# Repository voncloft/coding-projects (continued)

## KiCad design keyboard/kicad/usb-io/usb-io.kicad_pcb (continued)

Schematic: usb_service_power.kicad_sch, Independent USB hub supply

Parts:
C50: 10uF 50V X7R; C_1206_3216Metric; MPN CL31B106KBHNNNE; JLCPCB C89632
C51: 100nF 50V X7R; C_0603_1608Metric; MPN CC0603KRX7R9BB104; JLCPCB C14663
C52, C53: 22uF 25V X7R; C_1210_3225Metric; MPN GRM32ER71E226KE15K; JLCPCB C5646288
D10, D11, D12: SS14; D_SMA; MPN SS14; JLCPCB C2480
L1: 4.7uH 4.6A Irms 6A Isat; L_Bourns_SRP5030T; MPN SRP5030T-4R7M
U2: AP63203WU-7; TSOT-23-6; MPN AP63203WU-7; JLCPCB C780769

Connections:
+3V3_HUB: C52.1, C53.1, L1.2, U2.1 (FB); also elsewhere on the board
+5V_CORE: D10.2 (A); also elsewhere on the board
GND: C50.2, C52.2, C53.2, U2.4 (GND); also elsewhere on the board
HUB_BST: C51.1, U2.6 (BST)
HUB_SW: C51.2, L1.1, U2.5 (SW)
PC_VBUS: D11.2 (A); also elsewhere on the board
PD_RAW: D12.2 (A); also elsewhere on the board
SERVICE_IN: C50.1, D10.1 (K), D11.1 (K), D12.1 (K), U2.2 (EN), U2.3 (IN)

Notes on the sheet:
AP63203 fixed 3.3 V. Sources are isolated by 40 V Schottky diodes. The hub stays powered from the connected host/charger during RP2040 reset. Do not connect sources directly.

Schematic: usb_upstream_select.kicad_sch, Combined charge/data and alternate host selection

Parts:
C54, C55: 100nF 50V X7R; C_0603_1608Metric; MPN CC0603KRX7R9BB104; JLCPCB C14663
R54: 10k 1%; R_0603_1608Metric; MPN 0603WAF1002T5E; JLCPCB C25804
R55: 15k 1%; R_0603_1608Metric; MPN 0603WAF1502T5E
U40: TS3USB221ARSER; Texas_UQFN-10_1.5x2mm_P0.5mm; MPN TS3USB221ARSER; JLCPCB C128396
U42: USBLC6-2SC6; SOT-23-6; MPN USBLC6-2SC6; JLCPCB C7519

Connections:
+3V3_HUB: C54.1, C55.1, U40.10 (VCC), U42.5 (VBUS); also elsewhere on the board
CHARGE_DM: U40.2 (1D-), U42.1 (I/O1), U42.6 (I/O1); also elsewhere on the board
CHARGE_DP: U40.1 (1D+), U42.3 (I/O2), U42.4 (I/O2); also elsewhere on the board
GND: C54.2, C55.2, R55.2, U40.5 (GND), U40.6 (OE_N), U42.2 (GND); also elsewhere on the board
PC_DM: U40.4 (2D-); also elsewhere on the board
PC_DP: U40.3 (2D+); also elsewhere on the board
PC_SELECT: R54.2, R55.1, U40.9 (S)
PC_VBUS: R54.1; also elsewhere on the board
UP_DM: U40.7 (D-); also elsewhere on the board
UP_DP: U40.8 (D+); also elsewhere on the board

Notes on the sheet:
Port 1: charging USB-C data. Port 2: existing PC DATA connector. PC takes priority when both are plugged in. Only data is selected; VBUS rails stay isolated. HUSB238 DP/DM are deliberately not connected; USB PD remains on CC1/CC2.

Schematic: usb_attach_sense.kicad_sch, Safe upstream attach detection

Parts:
C56: 100nF 50V X7R; C_0603_1608Metric; MPN CC0603KRX7R9BB104; JLCPCB C14663
Q10, Q11: MMBT3904; SOT-23; MPN MMBT3904; JLCPCB C20526
R50: 220k 1%; R_0603_1608Metric; MPN 0603WAF2203T5E
R51, R52, R53: 100k 1%; R_0603_1608Metric; MPN 0603WAF1003T5E; JLCPCB C25803
R56: 10k 1%; R_0603_1608Metric; MPN 0603WAF1002T5E; JLCPCB C25804
U41: SN74LVC1G04DBVR; SOT-23-5; MPN SN74LVC1G04DBVR

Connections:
+3V3_HUB: C56.1, R56.1, U41.5 (VCC); also elsewhere on the board
GND: C56.2, Q10.2 (E), Q11.2 (E), R51.2, R53.2, U41.3 (GND); also elsewhere on the board
PC_SENSE_BASE: Q11.1 (B), R52.2, R53.1
PC_VBUS: R52.1; also elsewhere on the board
PD_RAW: R50.1; also elsewhere on the board
PD_SENSE_BASE: Q10.1 (B), R50.2, R51.1
UPSTREAM_ABSENT: Q10.3 (C), Q11.3 (C), R56.2, U41.2
UPSTREAM_PRESENT: U41.4; also elsewhere on the board

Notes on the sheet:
Two NPN collectors implement OR presence detection without coupling source VBUS rails. 3.3 V logic drives hub VBUS_DET; the PD input can be 20 V and must never connect directly to this pin.

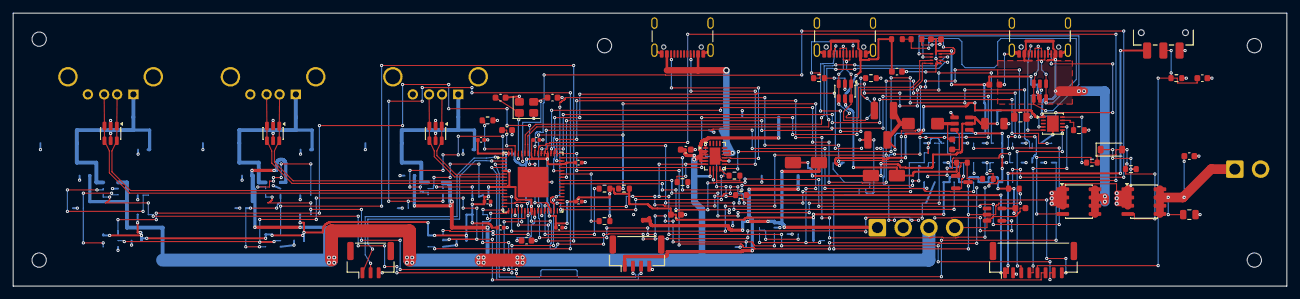
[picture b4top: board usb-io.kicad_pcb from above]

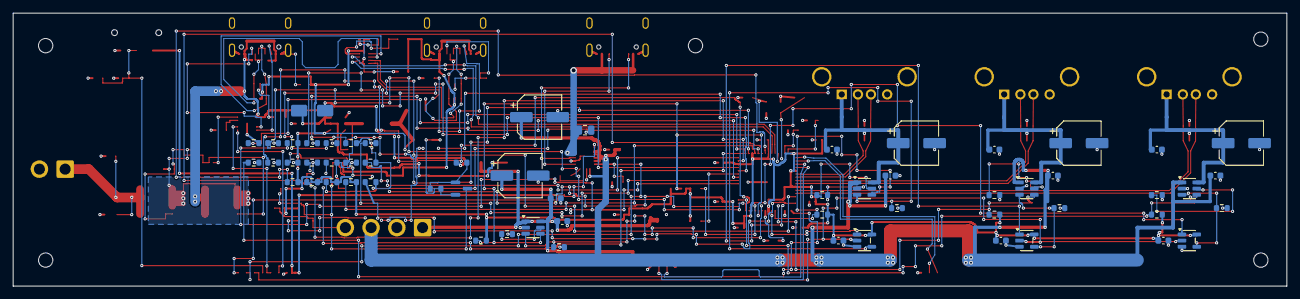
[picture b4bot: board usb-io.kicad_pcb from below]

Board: 4 copper layers, 196.0 x 42.0 mm, 138 parts (59 on the bottom side), 96 nets.

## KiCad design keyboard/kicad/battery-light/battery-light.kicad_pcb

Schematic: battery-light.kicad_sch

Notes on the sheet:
Tiny two-colour battery indicator
Rev F integrated keyboard computer. See validation reports.

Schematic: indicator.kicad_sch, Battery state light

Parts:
D1: RED; LED_0603_1608Metric; MPN LTST-C190KRKT
D2: GREEN; LED_0603_1608Metric; MPN LTST-C190KGKT
H1, H2: M2 clearance; MountingHole_2.2mm_M2
J1: To control J5; JST_GH_BM03B-GHS-TBT_1x03-1MP_P1.25mm_Vertical
R1, R2: 680 1%; R_0603_1608Metric

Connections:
GND: D1.1 (K), D2.1 (K), J1.3
GREEN_A: D2.2 (A), R2.2
GREEN_PWM: J1.2, R2.1
RED_A: D1.2 (A), R1.2
RED_PWM: J1.1, R1.1

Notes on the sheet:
Two adjacent 0603 LEDs feed one diffused light pipe above the display. Green 80-100%; both channels yellow 30-79%; red 0-29%. Each GPIO is current limited locally. The always-on controller supplies PWM; this indicator remains available when key RGB is off.

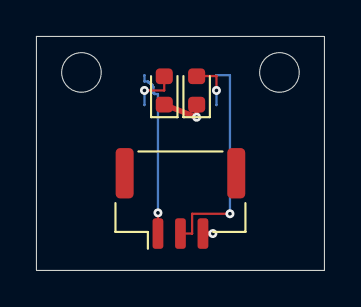
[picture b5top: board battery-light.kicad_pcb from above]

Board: 4 copper layers, 16.0 x 13.0 mm, 7 parts (2 on the bottom side), 5 nets.

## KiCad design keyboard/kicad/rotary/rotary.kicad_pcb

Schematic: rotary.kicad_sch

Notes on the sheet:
Rotary input: 30 detents, push button
Rev F integrated keyboard computer. See validation reports.

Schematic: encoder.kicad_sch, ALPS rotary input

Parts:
C1, C2, C3: 10n 25V; C_0603_1608Metric
H1, H2, H3, H4: M2 clearance; MountingHole_2.2mm_M2
J1: To control J4; JST_GH_BM05B-GHS-TBT_1x05-1MP_P1.25mm_Vertical
R1, R2, R3: 2.2k 1%; R_0603_1608Metric
SW1: EC11E15244G1; ALPS_EC11E15244G1; MPN EC11E15244G1

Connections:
+3V3_AON: J1.1, R1.1, R2.1, R3.1
ENC_A: C1.1, J1.3, R1.2, SW1.A
ENC_B: C2.1, J1.4, R2.2, SW1.B
ENC_SW: C3.1, J1.5, R3.2, SW1.S1
GND: C1.2, C2.2, C3.2, J1.2, SW1.C, SW1.S2

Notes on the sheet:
EC11E15244G1: 30 detents, 15 pulses, push switch. 2.2k pullups provide >1mA contact current. 10nF capacitors suppress contact noise; firmware decodes two transitions per detent.

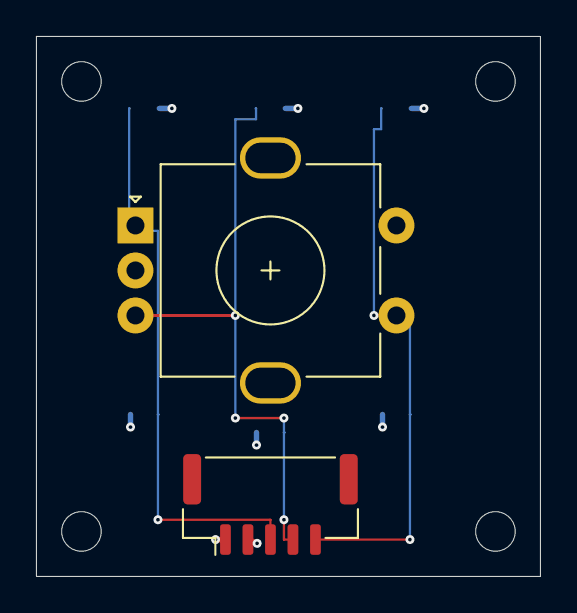
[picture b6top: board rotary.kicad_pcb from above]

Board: 4 copper layers, 28.0 x 30.0 mm, 12 parts (6 on the bottom side), 5 nets.

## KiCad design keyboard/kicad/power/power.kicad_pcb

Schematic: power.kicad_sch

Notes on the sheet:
Rev E: USB-C 2S battery charging and regulated power distribution
Rev E. USB and power circuitry. Read CHECKS.md for validation status.

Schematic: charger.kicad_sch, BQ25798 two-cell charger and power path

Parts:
C1, C2, C3, C4, C5: 10u 50V X7R; C_1206_3216Metric
C6, C7, C8, C9, C10, C11, C12: 10u 25V X7R; C_1206_3216Metric
L1: 1uH Isat>=12A; L_7x7; MPN SRP7050TA-1R0M
U1: BQ25798RQMR; Texas_RQM0029A_VQFN-29_4x4mm_P0.4mm; MPN BQ25798RQMR; JLCPCB C2876593

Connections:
BAT: C11.1, C12.1, U1.22 (BAT), U1.23 (BAT); also elsewhere on the board
BATT_TS: U1.16 (TS); also elsewhere on the board
BAT_SENSE: U1.18 (BATP); also elsewhere on the board
CHG_BTST1: U1.4 (BTST1); also elsewhere on the board
CHG_BTST2: U1.19 (BTST2); also elsewhere on the board
CHG_CE_N: U1.13 (~CE); also elsewhere on the board
CHG_ILIM: U1.17 (ILIM_HIZ); also elsewhere on the board
CHG_PROG: U1.20 (PROG); also elsewhere on the board
CHG_STAT: U1.1 (STAT); also elsewhere on the board
CHG_SW1: L1.1, U1.28 (SW1); also elsewhere on the board
CHG_SW2: L1.2, U1.26 (SW2); also elsewhere on the board
GND: C1.2, C2.2, C3.2, C4.2, C5.2, C6.2, C7.2, C8.2, C9.2, C10.2, C11.2, C12.2, U1.10 (ACDRV2), U1.11 (ACDRV1), U1.27 (GND); also elsewhere on the board
I2C_SCL: U1.14 (SCL); also elsewhere on the board
I2C_SDA: U1.15 (SDA); also elsewhere on the board
PD_IN_FUSED: C1.1, C2.1, U1.2 (VBUS), U1.3 (VBUS), U1.8 (VAC2), U1.9 (VAC1); also elsewhere on the board
PMID: C3.1, C4.1, C5.1, U1.29 (PMID); also elsewhere on the board
POWER_IRQ: U1.21 (~INT); also elsewhere on the board
REGN: U1.5 (REGN); also elsewhere on the board
SDRV: U1.24 (SDRV); also elsewhere on the board
SYS: C6.1, C7.1, C8.1, C9.1, C10.1, U1.25 (SYS); also elsewhere on the board

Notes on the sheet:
2S Li-ion only: 8.4 V termination, 6.04 kOhm PROG, 1.5 MHz. Requires a protected, balanced 2S pack and 103AT-2 10k NTC on the cells. CE defaults disabled. Firmware validates PD contract, programs limits, checks temperature and then enables charging.

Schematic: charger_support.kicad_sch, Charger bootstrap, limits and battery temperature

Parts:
C13, C14, C15: 100n 50V; C_0402_1005Metric
C16, C17: 47n 25V; C_0402_1005Metric
C18: 4.7u 10V; C_0805_2012Metric
C19: 1n 50V; C_0402_1005Metric
C20: 47n 25V; C_0603_1608Metric
D1: BAT54; D_SOD-123; MPN BAT54W
Q1: 2N7002; SOT-23; MPN 2N7002; JLCPCB C8545
R1: 6.04k 1%; R_0603_1608Metric
R2: 100; R_0603_1608Metric
R3: 5.23k 1%; R_0603_1608Metric
R4: 30.1k 1%; R_0603_1608Metric
R5: 365k 1%; R_0603_1608Metric
R6: 100k 1%; R_0603_1608Metric
R7, R8, R9: 10k; R_0603_1608Metric
R10: 1k; R_0603_1608Metric
R11: 100k; R_0603_1608Metric

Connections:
+3V3_AON: R8.2, R9.2; also elsewhere on the board
BAT: R2.1; also elsewhere on the board
BATT_TS: R3.2, R4.1; also elsewhere on the board
BAT_SENSE: C20.1, R2.2; also elsewhere on the board
BOOST_DIODE: D1.2 (A), R10.2
CHARGE_ENABLE: Q1.1 (G), R11.1; also elsewhere on the board
CHG_BTST1: C16.1; also elsewhere on the board
CHG_BTST2: C17.1; also elsewhere on the board
CHG_CE_N: Q1.3 (D), R7.1; also elsewhere on the board
CHG_ILIM: D1.1 (K), R5.2, R6.1; also elsewhere on the board
CHG_PROG: R1.1; also elsewhere on the board
CHG_STAT: R8.1; also elsewhere on the board
CHG_SW1: C16.2; also elsewhere on the board
CHG_SW2: C17.2; also elsewhere on the board
GND: C13.2, C14.2, C15.2, C18.2, C19.2, C20.2, Q1.2 (S), R1.2, R4.2, R6.2, R11.2; also elsewhere on the board
INPUT_BOOST: R10.1; also elsewhere on the board
PD_IN_FUSED: C15.1; also elsewhere on the board
PMID: C13.1; also elsewhere on the board
POWER_IRQ: R9.1; also elsewhere on the board
REGN: C18.1, R3.1, R5.1, R7.2; also elsewhere on the board
SDRV: C19.1; also elsewhere on the board
SYS: C14.1; also elsewhere on the board

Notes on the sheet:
REGN divider limits default input current. A diode from INPUT_BOOST raises the hardware ceiling only after configuration. TS uses 5.23k pullup and 30.1k parallel return with external 103AT-2. Open/short NTC inhibits charging. No ship FET: SDRV has the specified 1nF capacitor.

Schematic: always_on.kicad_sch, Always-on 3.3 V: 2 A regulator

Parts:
C21: 10uF 50V X7R; C_1206_3216Metric; MPN CL31B106KBHNNNE; JLCPCB C89632
C22: 100nF 50V X7R; C_0603_1608Metric; MPN CC0603KRX7R9BB104; JLCPCB C14663
C23, C61: 22uF 25V X7R; C_1210_3225Metric; MPN GRM32ER71E226KE15K; JLCPCB C5646288
L2: 4.7uH 4.6A Irms 6A Isat; L_Bourns_SRP5030T; MPN SRP5030T-4R7M; JLCPCB C2045677
U2: AP63203WU-7; TSOT-23-6; MPN AP63203WU-7; JLCPCB C780769

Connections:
+3V3_AON: C23.1, C61.1, L2.2, U2.1 (FB); also elsewhere on the board
AON_BST: C22.1, U2.6 (BST)
AON_SW: C22.2, L2.1, U2.5 (SW)
GND: C21.2, C23.2, C61.2, U2.4 (GND); also elsewhere on the board
SYS: C21.1, U2.2 (EN), U2.3 (IN); also elsewhere on the board

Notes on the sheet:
AP63203 fixed 3.3 V. 2 A regulator capacity; actual rail load must be measured. VIN/EN are SYS rated. No low-voltage SLEEP pin is tied to the 2S rail. Tight input/ground/bootstrap loops; short SW and Kelvin output feedback.

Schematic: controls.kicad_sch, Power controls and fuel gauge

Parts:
C24, C25: 100n 25V; C_0402_1005Metric
R12, R13, R14, R15, R16, R17, R18: 100k; R_0603_1608Metric
U3: TCA9534PWR; TSSOP-16_4.4x5mm_P0.65mm; MPN TCA9534PWR
U4: MAX17049G+T10; TDFN-8-1EP_2x2mm_P0.5mm_EP0.8x1.2mm; MPN MAX17049G+T10; JLCPCB C18185545

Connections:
+3V3_AON: C24.1, C25.1, U3.16 (VDD), U4.3 (VDD); also elsewhere on the board
AUDIO_ENABLE: R17.1, U3.10 (P5); also elsewhere on the board
BAT: U4.2 (CELL); also elsewhere on the board
CHARGE_ENABLE: U3.5 (P1); also elsewhere on the board
EXT_USB_ENABLE: R15.1, U3.7 (P3); also elsewhere on the board
GND: C24.2, C25.2, R12.2, R13.2, R14.2, R15.2, R16.2, R17.2, R18.2, U3.1 (A0), U3.2 (A1), U3.3 (A2), U3.8 (GND), U4.1 (CTG), U4.4 (GND), U4.6 (QSTRT), U4.9 (EP); also elsewhere on the board
I2C_SCL: U3.14 (SCL), U4.7 (SCL); also elsewhere on the board
I2C_SDA: U3.15 (SDA), U4.8 (SDA); also elsewhere on the board
INPUT_BOOST: R13.1, U3.4 (P0); also elsewhere on the board
IO_RAIL_ENABLE: R18.1, U3.11 (P6); also elsewhere on the board
MAIN_ENABLE: R12.1; also elsewhere on the board
POWER_IRQ: U3.13 (~INT), U4.5 (ALRT_N); also elsewhere on the board
RGB_ENABLE: R16.1, U3.9 (P4); also elsewhere on the board
WATCH_ENABLE: R14.1, U3.6 (P2); also elsewhere on the board
WATCH_FAULT_N: U3.12 (P7); also elsewhere on the board

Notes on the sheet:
TCA9534 at 0x20; power-on pins are inputs with external pulldowns. MAX17049 at 0x36 senses the protected 2S pack; its VDD is regulated 3.3 V. MAIN_ENABLE is RP2040 GPIO23. POWER_REQUEST is the rear ON/OFF request.

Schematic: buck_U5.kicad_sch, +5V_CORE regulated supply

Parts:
C26, C27: 22u 25V X7R; C_1210_3225Metric
C28, C29, C30, C31: 47u 16V X5R; C_1210_3225Metric
C32, C33: 100n 25V; C_0402_1005Metric
C34: 1u 10V; C_0402_1005Metric
C35: 10n 25V; C_0402_1005Metric
C36: 220p C0G; C_0603_1608Metric
L3: 2.2uH Isat>=14A; L_7x7; MPN SRP7050TA-2R2M
R19: 300k 1%; R_0603_1608Metric
R20: 43k 1%; R_0603_1608Metric
R21: 75k 0.1%; R_0603_1608Metric
R22: 10k 0.1%; R_0603_1608Metric
R23: 100k; R_0603_1608Metric
U5: TPS568230RJER; Texas_RJE0020A_VQFN-20-1EP_3x3mm_P0.45mm_EP0.675x0.76mm; MPN TPS568230RJER

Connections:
+3V3_AON: R23.2; also elsewhere on the board
+5V_CORE: C28.1, C29.1, C30.1, C31.1, C36.1, L3.2, R21.1; also elsewhere on the board
GND: C26.2, C27.2, C28.2, C29.2, C30.2, C31.2, C32.2, C34.2, C35.2, R20.2, R22.2, U5.7 (GND), U5.8 (GND), U5.13 (AGND), U5.18 (GND), U5.21 (GND); also elsewhere on the board
MAIN_ENABLE: U5.12 (EN); also elsewhere on the board
SYS: C26.1, C27.1, C32.1, U5.2 (VIN), U5.3 (VIN), U5.4 (VIN), U5.5 (VIN); also elsewhere on the board
U5_BST: C33.1, U5.1 (BST)
U5_FB: C36.2, R21.2, R22.1, U5.14 (FB)
U5_MODE: R19.2, R20.1, U5.15 (MODE)
U5_PG: R23.1, U5.9 (PGOOD)
U5_SS: C35.1, U5.11 (SS)
U5_SW: C33.2, L3.1, U5.6 (SW), U5.19 (SW), U5.20 (SW)
U5_VCC: C34.1, R19.1, U5.17 (VCC)

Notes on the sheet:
TPS568230, 600 kHz out-of-audio mode. Input is 2S system rail, never the 20 V PD input. Power-current loops are routed locally; firmware enforces the shared input-power budget.

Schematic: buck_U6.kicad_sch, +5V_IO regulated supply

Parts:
C37, C38: 22u 25V X7R; C_1210_3225Metric
C39, C40, C41, C42: 47u 16V X5R; C_1210_3225Metric
C43, C44: 100n 25V; C_0402_1005Metric
C45: 1u 10V; C_0402_1005Metric
C46: 10n 25V; C_0402_1005Metric
C47: 220p C0G; C_0603_1608Metric
L4: 2.2uH Isat>=14A; L_7x7; MPN SRP7050TA-2R2M
R24: 300k 1%; R_0603_1608Metric
R25: 43k 1%; R_0603_1608Metric
R26: 75k 0.1%; R_0603_1608Metric
R27: 10k 0.1%; R_0603_1608Metric
R28: 100k; R_0603_1608Metric
U6: TPS568230RJER; Texas_RJE0020A_VQFN-20-1EP_3x3mm_P0.45mm_EP0.675x0.76mm; MPN TPS568230RJER

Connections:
+3V3_AON: R28.2; also elsewhere on the board
+5V_IO: C39.1, C40.1, C41.1, C42.1, C47.1, L4.2, R26.1; also elsewhere on the board
GND: C37.2, C38.2, C39.2, C40.2, C41.2, C42.2, C43.2, C45.2, C46.2, R25.2, R27.2, U6.7 (GND), U6.8 (GND), U6.13 (AGND), U6.18 (GND), U6.21 (GND); also elsewhere on the board
IO_RAIL_ENABLE: U6.12 (EN); also elsewhere on the board
SYS: C37.1, C38.1, C43.1, U6.2 (VIN), U6.3 (VIN), U6.4 (VIN), U6.5 (VIN); also elsewhere on the board
U6_BST: C44.1, U6.1 (BST)
U6_FB: C47.2, R26.2, R27.1, U6.14 (FB)
U6_MODE: R24.2, R25.1, U6.15 (MODE)
U6_PG: R28.1, U6.9 (PGOOD)
U6_SS: C46.1, U6.11 (SS)
U6_SW: C44.2, L4.1, U6.6 (SW), U6.19 (SW), U6.20 (SW)
U6_VCC: C45.1, R24.1, U6.17 (VCC)

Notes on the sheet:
TPS568230, 600 kHz out-of-audio mode. Input is 2S system rail, never the 20 V PD input. Power-current loops are routed locally; firmware enforces the shared input-power budget.

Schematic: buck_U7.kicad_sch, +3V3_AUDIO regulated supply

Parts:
C48, C49: 22u 25V X7R; C_1210_3225Metric
C50, C51, C52, C53: 47u 16V X5R; C_1210_3225Metric
C54, C55: 100n 25V; C_0402_1005Metric
C56: 1u 10V; C_0402_1005Metric
C57: 10n 25V; C_0402_1005Metric
C58: 220p C0G; C_0603_1608Metric
L5: 1.5uH Isat>=14A; L_7x7; MPN SRP7050TA-1R5M
R29: 300k 1%; R_0603_1608Metric
R30: 43k 1%; R_0603_1608Metric
R31: 45k 0.1%; R_0603_1608Metric
R32: 10k 0.1%; R_0603_1608Metric
R33: 100k; R_0603_1608Metric
U7: TPS568230RJER; Texas_RJE0020A_VQFN-20-1EP_3x3mm_P0.45mm_EP0.675x0.76mm; MPN TPS568230RJER

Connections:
+3V3_AON: R33.2; also elsewhere on the board
+3V3_AUDIO: C50.1, C51.1, C52.1, C53.1, C58.1, L5.2, R31.1; also elsewhere on the board
AUDIO_ENABLE: U7.12 (EN); also elsewhere on the board
GND: C48.2, C49.2, C50.2, C51.2, C52.2, C53.2, C54.2, C56.2, C57.2, R30.2, R32.2, U7.7 (GND), U7.8 (GND), U7.13 (AGND), U7.18 (GND), U7.21 (GND); also elsewhere on the board
SYS: C48.1, C49.1, C54.1, U7.2 (VIN), U7.3 (VIN), U7.4 (VIN), U7.5 (VIN); also elsewhere on the board
U7_BST: C55.1, U7.1 (BST)
U7_FB: C58.2, R31.2, R32.1, U7.14 (FB)
U7_MODE: R29.2, R30.1, U7.15 (MODE)
U7_PG: R33.1, U7.9 (PGOOD)
U7_SS: C57.1, U7.11 (SS)
U7_SW: C55.2, L5.1, U7.6 (SW), U7.19 (SW), U7.20 (SW)
U7_VCC: C56.1, R29.1, U7.17 (VCC)

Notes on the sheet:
TPS568230, 600 kHz out-of-audio mode. Input is 2S system rail, never the 20 V PD input. Power-current loops are routed locally; firmware enforces the shared input-power budget.

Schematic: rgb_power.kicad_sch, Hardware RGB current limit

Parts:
C59: 100n 25V; C_0603_1608Metric
C60: 10u 10V; C_0805_2012Metric
R34: 30.1k 1%; R_0603_1608Metric
R35: 100k; R_0603_1608Metric
R36: 10k; R_0603_1608Metric
U8: TPS2553DBVR; SOT-23-6; MPN TPS2553DBVR; JLCPCB C55266

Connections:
+3V3_AON: R36.2; also elsewhere on the board
+5V_CORE: C59.1, U8.1 (IN); also elsewhere on the board
+5V_RGB: C60.1, U8.6 (OUT); also elsewhere on the board
+5V_RGB_ILIM: R34.1, U8.5 (ILIM)
GND: C59.2, C60.2, R34.2, R35.2, U8.2 (GND); also elsewhere on the board
RGB_ENABLE: R35.1, U8.3 (EN); also elsewhere on the board
RGB_FAULT_N: R36.1, U8.4 (FAULT_N)

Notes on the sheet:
TPS2553 30.1k current limit protects the RGB rail and 1 A GH contact. Software RGB budget is 0.7 A for 108 keys plus the battery pixel. Full-brightness all-white is not supported.

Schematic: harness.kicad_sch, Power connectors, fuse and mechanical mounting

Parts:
F1: 3A 32V; Fuse_1206_3216Metric; MPN 0466003.NRHF; JLCPCB C14165
F2: 10A 32V; Fuse_1206_3216Metric; MPN 0458010.DR
H1, H2, H3, H4: M2 clearance; MountingHole_2.2mm_M2
J1: From rear J9; JST_VH_B2P-VH_1x02_P3.96mm_Vertical
J2: To rear J10; JST_VH_B4P-VH_1x04_P3.96mm_Vertical
J3: To rear J11; JST_GH_BM08B-GHS-TBT_1x08-1MP_P1.25mm_Vertical
J4: To keyboard J3; JST_GH_BM08B-GHS-TBT_1x08-1MP_P1.25mm_Vertical
J5: To keyboard J4 pins 3/4/5/6; JST_GH_BM04B-GHS-TBT_1x04-1MP_P1.25mm_Vertical
J6: CM4 / display supply; JST_VH_B2P-VH_1x02_P3.96mm_Vertical
J7: To audio J3 pins 1/2; JST_VH_B2P-VH_1x02_P3.96mm_Vertical
J8: Protected 2S battery; JST_VH_B2P-VH_1x02_P3.96mm_Vertical
J9: Cell-mounted 103AT-2 NTC; JST_GH_BM02B-GHS-TBT_1x02-1MP_P1.25mm_Vertical

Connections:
+3V3_AON: J3.1, J4.1, J5.3; also elsewhere on the board
+3V3_AUDIO: J7.1; also elsewhere on the board
+5V_CORE: J2.1, J6.1; also elsewhere on the board
+5V_IO: J2.3; also elsewhere on the board
+5V_RGB: J4.3; also elsewhere on the board
BAT: F2.2; also elsewhere on the board
BATT_TS: J9.1; also elsewhere on the board
BAT_PACK: F2.1, J8.1
EXT_USB_ENABLE: J3.6; also elsewhere on the board
GND: J1.2, J2.2, J2.4, J3.2, J4.2, J4.4, J4.8, J5.4, J6.2, J7.2, J8.2, J9.2; also elsewhere on the board
I2C_SCL: J3.4, J5.2; also elsewhere on the board
I2C_SDA: J3.3, J5.1; also elsewhere on the board
MAIN_ENABLE: J4.6; also elsewhere on the board
PD_IN: F1.1, J1.1
PD_IN_FUSED: F1.2; also elsewhere on the board
POWER_IRQ: J4.7; also elsewhere on the board
POWER_REQUEST: J3.5, J4.5
WATCH_ENABLE: J3.7; also elsewhere on the board
WATCH_FAULT_N: J3.8; also elsewhere on the board

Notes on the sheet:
Protected 2S pack: 8.4 V max, >=10 A discharge capability, factory balancing/protection. J1 adapter power, J2 rear regulated power, J3 rear control, J4 keyboard power, J5 keyboard I2C, J6 CM4/display, J7 audio, J8 battery, J9 NTC. Power connector ratings and harness wire size must cover each load. 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

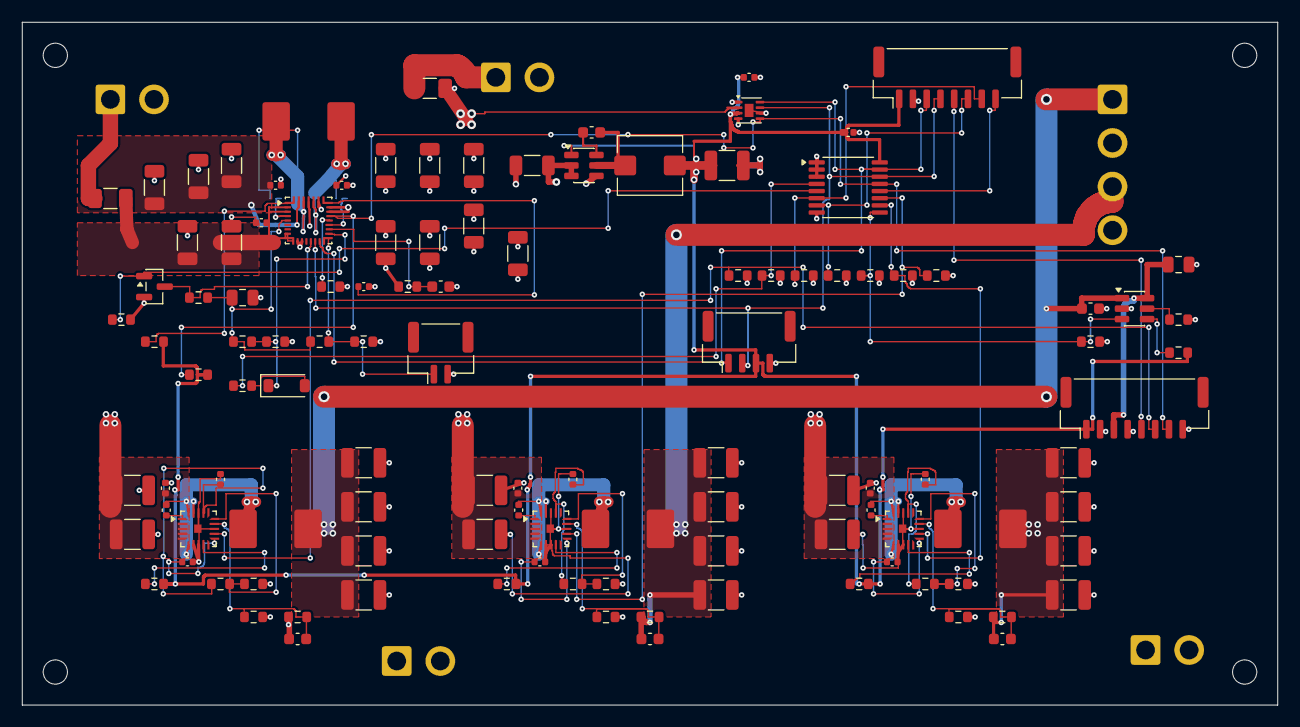
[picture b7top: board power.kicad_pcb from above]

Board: 4 copper layers, 114.0 x 62.0 mm, 127 parts (3 on the bottom side), 63 nets.

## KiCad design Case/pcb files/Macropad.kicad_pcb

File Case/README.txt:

General purpose: This is a macropad

This case needs to house a LCD screen on the underside of the case.

I've listed the URL of the LED screen in the Tab "Parts for Case"

The LCD will be soldered on the right side...so there will need to be a "breakout"
cable section on the far end of the board away from the rotary. Nothing can block
those soldered connections, 

There is a "reset" button on the U901 underneath it I provided the "reset" button
in the links as well under that tab.

Also a "on off" switch also provided URL and link in workbook. That will need to be on the side of case

I would prefer the case "snap" top and bottom

I added as much as i can about my pcb board in the pcb files folder

The case will also need to be "at a tilt" so the reset button is not pressed by accident

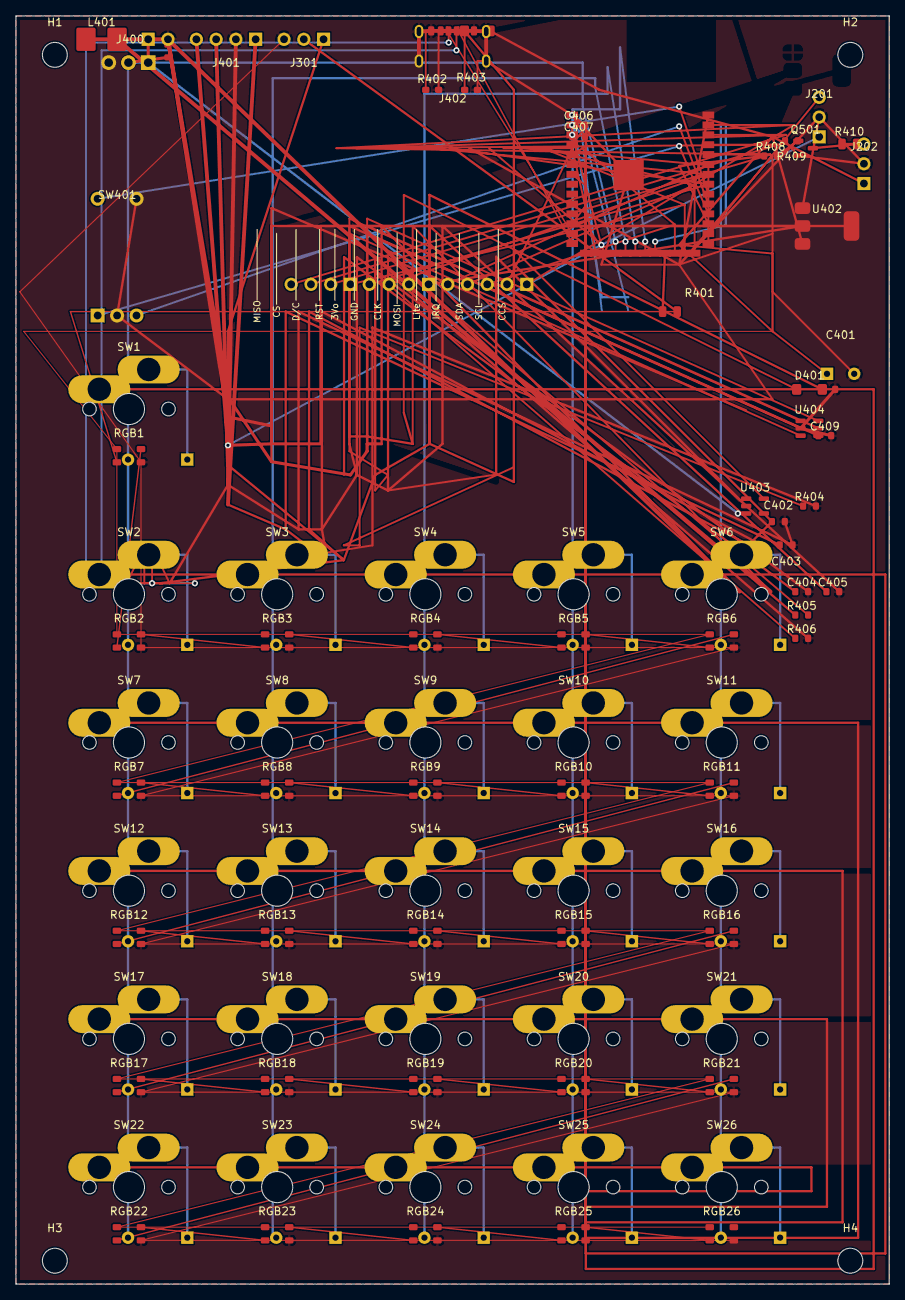
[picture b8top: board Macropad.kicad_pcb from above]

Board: 2 copper layers, 112.2 x 163.0 mm, 122 parts (28 on the bottom side), 98 nets.

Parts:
C401: 470uF; GEN_CP_Radial_D8_P3.5
C402: 1uF; C_0603_1608Metric_LOCAL
C403: 4.7uF; C_0603_1608Metric_LOCAL
C404, C405, C408, C409: 10uF; C_0603_1608Metric_LOCAL
C406: 100nF; C_0603_1608Metric_LOCAL
C407: 22uF; C_0603_1608Metric_LOCAL
D1, D2, D3, D4, D5, D6, D7, D8, D9, D10, D11, D12, D13, D14, D15, D16, D17, D18, D19, D20, D21, D22, D23, D24, D25, D26: D; D_DO35_Custom
D401: SS14; D_SOD123_LOCAL
D402: SS14_VBUS_TO_5VSYS; D_SOD123_LOCAL
F401: PTC_0.5A; R_0603_1608Metric_LOCAL
H1, H2, H3, H4: MountingHole; GEN_MountingHole_3.2mm_M3
J201: TSOP4838_C124647; GEN_PinHeader_1x3_P2.54
J202: IR_LED_TX_HDR; GEN_PinHeader_1x3_P2.54
J301: LED_CHAIN; GEN_PinHeader_1x3_P2.54
J302: LCD_SPI_PWRDATA; GEN_PinHeader_1x4_P2.54
J303: LCD_SPI_CTRL; GEN_PinHeader_1x4_P2.54
J304: TOUCH_I2C_SD_IRQ; GEN_PinHeader_1x5_P2.54
J400: BATTERY_LIPO; GEN_PinHeader_1x2_P2.54
J401: BAT_CHG_BOOST; GEN_PinHeader_1x4_P2.54
J402: USB_C_CHG_IN; USB_C_Receptacle_GCT_USB4125_6P_LOCAL
L401: 4.7uH; L_Boost_5x5_LOCAL
Q501: AO3400A; SOT-23_LOCAL
R401: 330R; R_0805_2012Metric_LOCAL
R402, R403: 5.1k; R_0603_1608Metric_LOCAL
R404: 3.3k; R_0603_1608Metric_LOCAL
R405: 162k; R_0603_1608Metric_LOCAL
R406: 22k; R_0603_1608Metric_LOCAL
R407: 10k; R_0603_1608Metric_LOCAL
R408: 100R; R_0603_1608Metric_LOCAL
R409: 100k; R_0603_1608Metric_LOCAL
R410: 47R; R_0805_2012Metric_LOCAL
RGB1, RGB2, RGB3, RGB4, RGB5, RGB6, RGB7, RGB8, RGB9, RGB10, RGB11, RGB12, RGB13, RGB14, RGB15, RGB16, RGB17, RGB18, RGB19, RGB20, RGB21, RGB22, RGB23, RGB24, RGB25, RGB26: SK6812MINI; RGB_PLACEHOLDER_3535
SW1, SW2, SW3, SW4, SW5, SW6, SW7, SW8, SW9, SW10, SW11, SW12, SW13, SW14, SW15, SW16, SW17, SW18, SW19, SW20, SW21, SW22, SW23, SW24, SW25, SW26: SW_Push; Kailh_Hotswap_MX_1U_Custom
SW401: RotaryEncoder_Switch; GEN_RotaryEncoder_EC11_Switch
SW402: MSS-102545-14A-V-SMT; SW_Slide_SPDT_BATTERY_KILL_MSS-102545-14A-V-SMT_LOCAL
SW402#2: SW_Push; SW_TACT_3x6_4P_LOCAL
U402: AP7361C-33E; SOT-223-3_TabPin2_LOCAL
U403: MCP73831; SOT-23-5_LOCAL
U404: MT3608; SOT-23-6_LOCAL
U901: ESP32-S3-WROOM-1-N8R8; ESP32-S3-WROOM-1_LOCAL

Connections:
3V3: C406.1, C407.1, J201.1, J302.1, J401.4, R407.2, U402.2, U901.2
5V_SYS: C401.1, C402.1, C405.1, C408.1, D401.2, D402.2, J202.1, J301.1, J401.3, R405.1, RGB1.1, RGB2.1, RGB3.1, RGB4.1, RGB5.1, RGB6.1, RGB7.1, RGB8.1, RGB9.1, RGB10.1, RGB11.1, RGB12.1, RGB13.1, RGB14.1, RGB15.1, RGB16.1, RGB17.1, RGB18.1, RGB19.1, RGB20.1, RGB21.1, RGB22.1, RGB23.1, RGB24.1, RGB25.1, RGB26.1, U402.3
BAT+: C403.1, C404.1, C409.1, F401.2, J401.1, L401.1, U404.4, U404.5
BAT_RAW: J400.1, SW402.1, U403.3
BAT_SW: F401.1, SW402.2
BOOST_FB: R405.2, R406.1, U404.3
BOOST_SW: D401.1, L401.2, U404.1, U404.6
CHG_PROG: R404.1, U403.5
COL0: D1.2, D2.2, D7.2, D12.2, D17.2, D22.2, U901.18
COL1: D3.2, D8.2, D13.2, D18.2, D23.2, U901.19
COL2: D4.2, D9.2, D14.2, D19.2, D24.2, U901.20
COL3: D5.2, D10.2, D15.2, D20.2, D25.2, U901.21
COL4: D6.2, D11.2, D16.2, D21.2, D26.2, U901.22
EN: R407.1, SW402#2.1, U901.3
ENC_A: SW401.A, U901.30
ENC_B: SW401.B, U901.31
ENC_SW: SW401.S1, U901.32
GND: C401.2, C402.2, C403.2, C404.2, C405.2, C406.2, C407.2, C408.2, C409.2, J201.2, J202.2, J301.3, J302.2, J400.2, J401.2, J402.A12, J402.B12, J402.S1, Q501.2, R402.2, R403.2, R404.2, R406.2, R409.2, RGB1.3, RGB2.3, RGB3.3, RGB4.3, RGB5.3, RGB6.3, RGB7.3, RGB8.3, RGB9.3, RGB10.3, RGB11.3, RGB12.3, RGB13.3, RGB14.3, RGB15.3, RGB16.3, RGB17.3, RGB18.3, RGB19.3, RGB20.3, RGB21.3, RGB22.3, RGB23.3, RGB24.3, RGB25.3, RGB26.3, SW401.C, SW401.S2, SW402#2.2, U402.1, U403.2, U404.2, U901.1, U901.40, U901.41
IR_LED_K: J202.3, R410.1
IR_LED_SW: Q501.3, R410.2
IR_RX: J201.3, U901.28
IR_TX: R408.1, U901.29
IR_TX_GATE: Q501.1, R408.2, R409.1
K1: D1.1, SW1.2
K2: D2.1, SW2.2
K3: D3.1, SW3.2
K4: D4.1, SW4.2
K5: D5.1, SW5.2
K6: D6.1, SW6.2
K7: D7.1, SW7.2
K8: D8.1, SW8.2
K9: D9.1, SW9.2
K10: D10.1, SW10.2
K11: D11.1, SW11.2
K12: D12.1, SW12.2
K13: D13.1, SW13.2
K14: D14.1, SW14.2
K15: D15.1, SW15.2
K16: D16.1, SW16.2
K17: D17.1, SW17.2
K18: D18.1, SW18.2
K19: D19.1, SW19.2
K20: D20.1, SW20.2
K21: D21.1, SW21.2
K22: D22.1, SW22.2
K23: D23.1, SW23.2
K24: D24.1, SW24.2
K25: D25.1, SW25.2
K26: D26.1, SW26.2
LCD_BL: J304.1, U901.39
LCD_CS: J303.2, U901.36
LCD_DC: J303.3, U901.37
LCD_MOSI: J302.4, U901.33
LCD_RST: J303.4, U901.38
LCD_SCLK: J302.3, U901.34
LED_DIN: J301.2, R401.2, RGB1.4
RGB1_DOUT: RGB1.2, RGB2.4
RGB2_DOUT: RGB2.2, RGB3.4
RGB3_DOUT: RGB3.2, RGB4.4
RGB4_DOUT: RGB4.2, RGB5.4
RGB5_DOUT: RGB5.2, RGB6.4
RGB6_DOUT: RGB6.2, RGB7.4
RGB7_DOUT: RGB7.2, RGB8.4
RGB8_DOUT: RGB8.2, RGB9.4
RGB9_DOUT: RGB9.2, RGB10.4
RGB10_DOUT: RGB10.2, RGB11.4
RGB11_DOUT: RGB11.2, RGB12.4
RGB12_DOUT: RGB12.2, RGB13.4
RGB13_DOUT: RGB13.2, RGB14.4
RGB14_DOUT: RGB14.2, RGB15.4
RGB15_DOUT: RGB15.2, RGB16.4
RGB16_DOUT: RGB16.2, RGB17.4
RGB17_DOUT: RGB17.2, RGB18.4
RGB18_DOUT: RGB18.2, RGB19.4
RGB19_DOUT: RGB19.2, RGB20.4
RGB20_DOUT: RGB20.2, RGB21.4
RGB21_DOUT: RGB21.2, RGB22.4
RGB22_DOUT: RGB22.2, RGB23.4
RGB23_DOUT: RGB23.2, RGB24.4
RGB24_DOUT: RGB24.2, RGB25.4
RGB25_DOUT: RGB25.2, RGB26.4
RGB_DATA: R401.1, U901.23
ROW0: SW1.1, U901.4
ROW1: SW2.1, SW3.1, SW4.1, SW5.1, SW6.1, U901.5
ROW2: SW7.1, SW8.1, SW9.1, SW10.1, SW11.1, U901.6
ROW3: SW12.1, SW13.1, SW14.1, SW15.1, SW16.1, U901.7
ROW4: SW17.1, SW18.1, SW19.1, SW20.1, SW21.1, U901.12
ROW5: SW22.1, SW23.1, SW24.1, SW25.1, SW26.1, U901.17
SD_CS: J304.5, U901.27
SPI_MISO: J303.1, U901.25
TOUCH_INT: J304.2, U901.16
TOUCH_SCL: J304.4, U901.26
TOUCH_SDA: J304.3, U901.24
USB_CC1: J402.A5, R402.1
USB_CC2: J402.B5, R403.1
USB_DN: J402.A7, J402.B7, U901.13
USB_DP: J402.A6, J402.B6, U901.14
VBUS: D402.1, J402.A9, J402.B9, U403.4
